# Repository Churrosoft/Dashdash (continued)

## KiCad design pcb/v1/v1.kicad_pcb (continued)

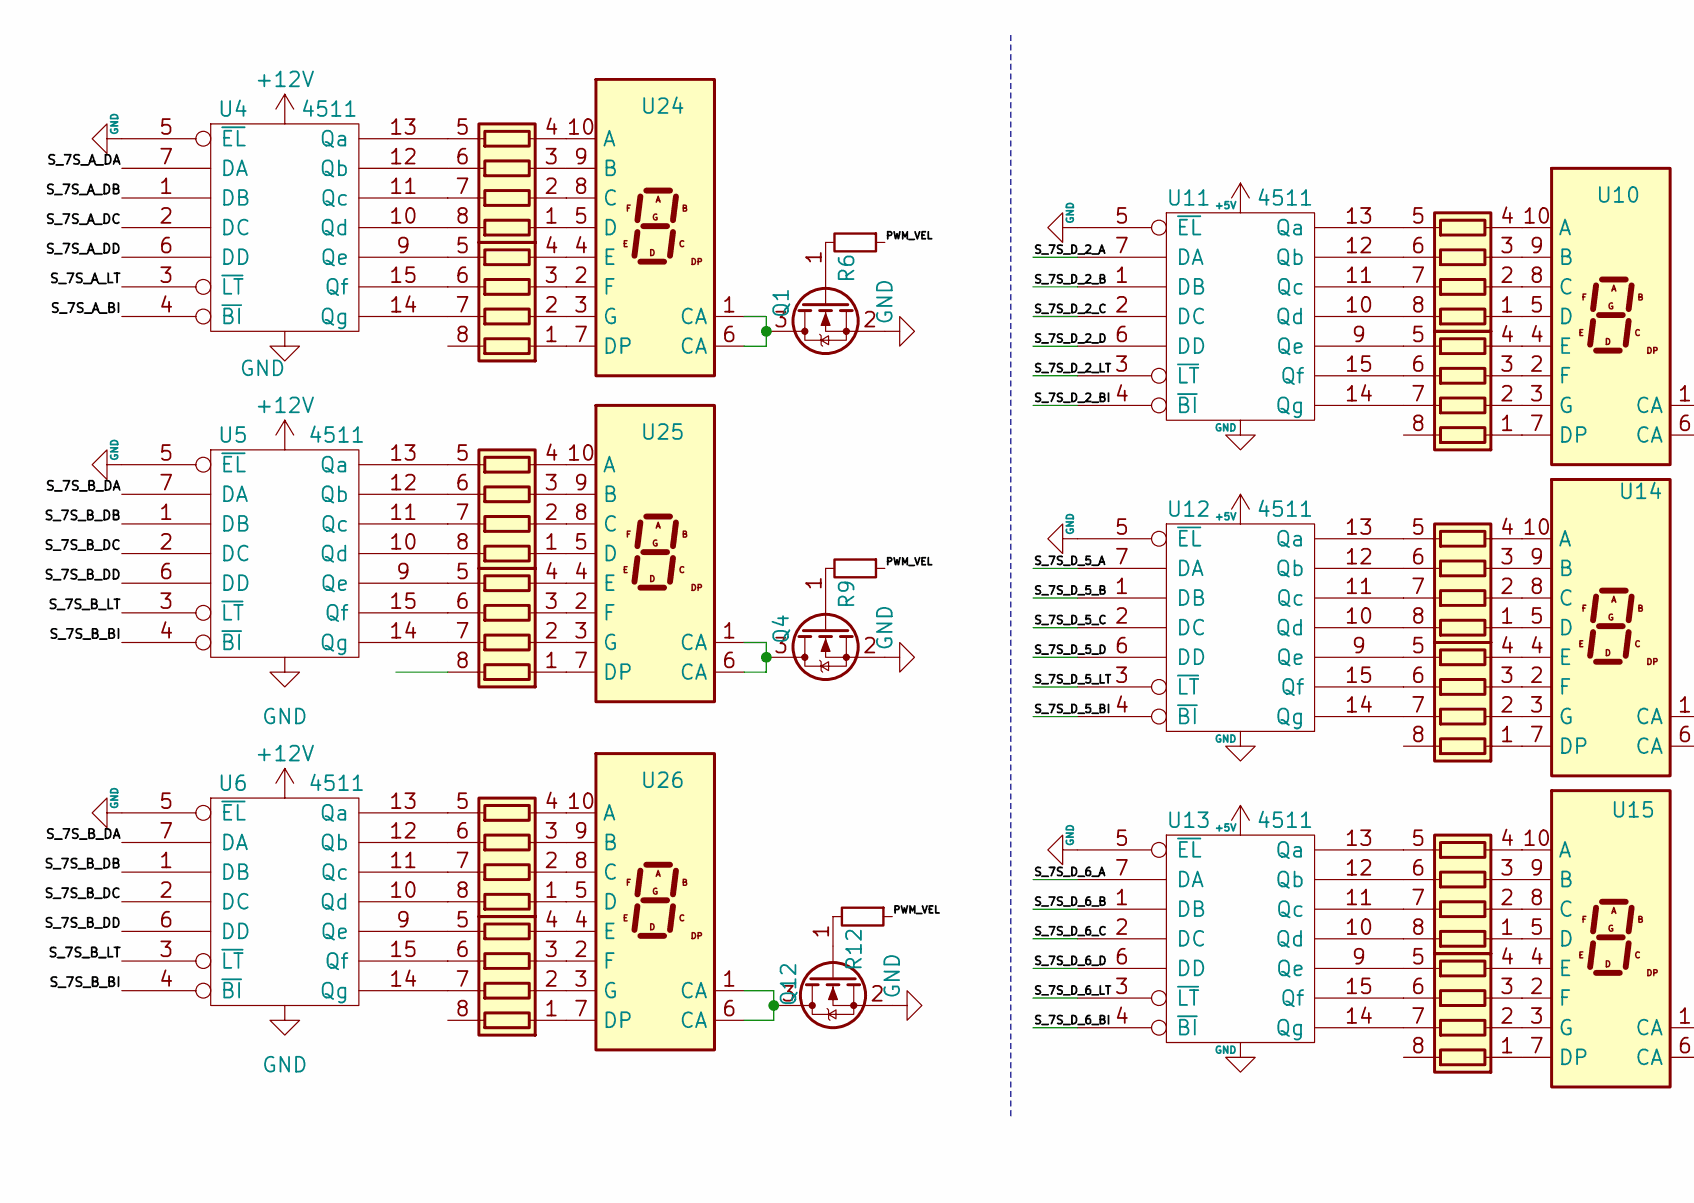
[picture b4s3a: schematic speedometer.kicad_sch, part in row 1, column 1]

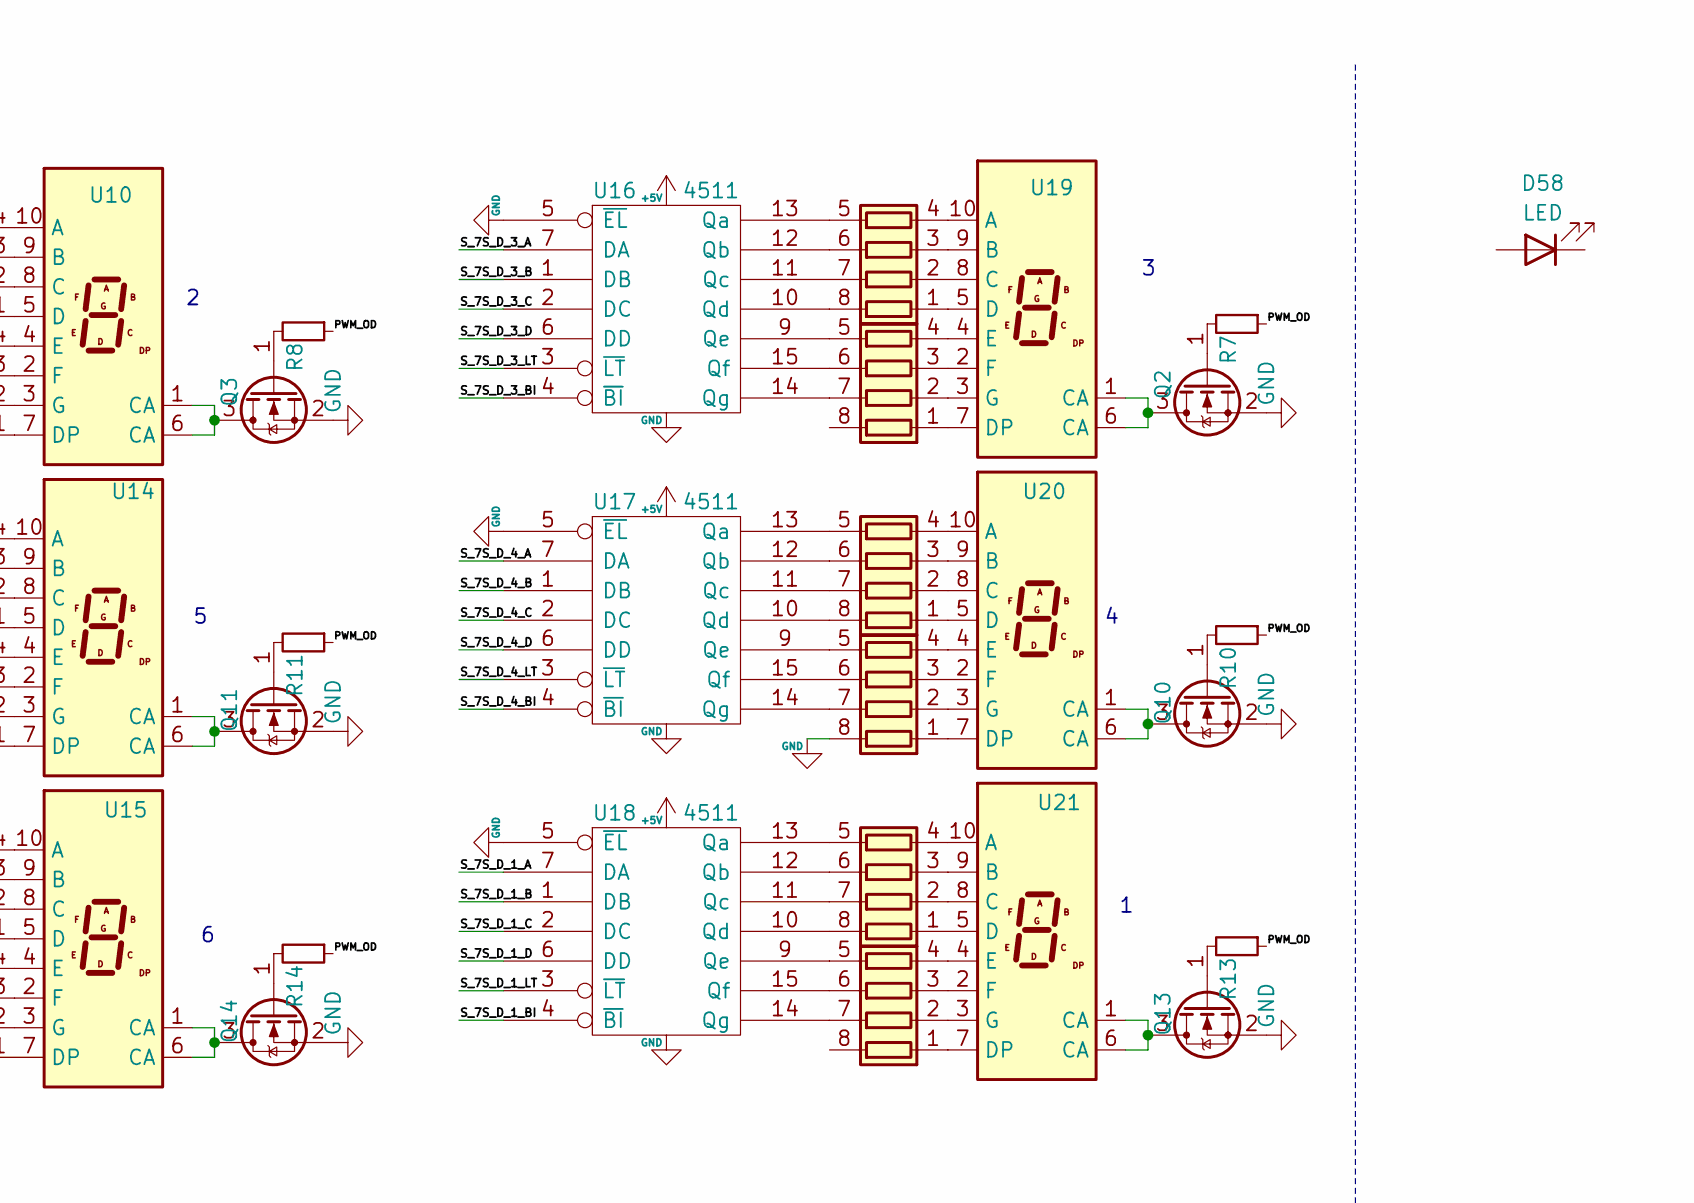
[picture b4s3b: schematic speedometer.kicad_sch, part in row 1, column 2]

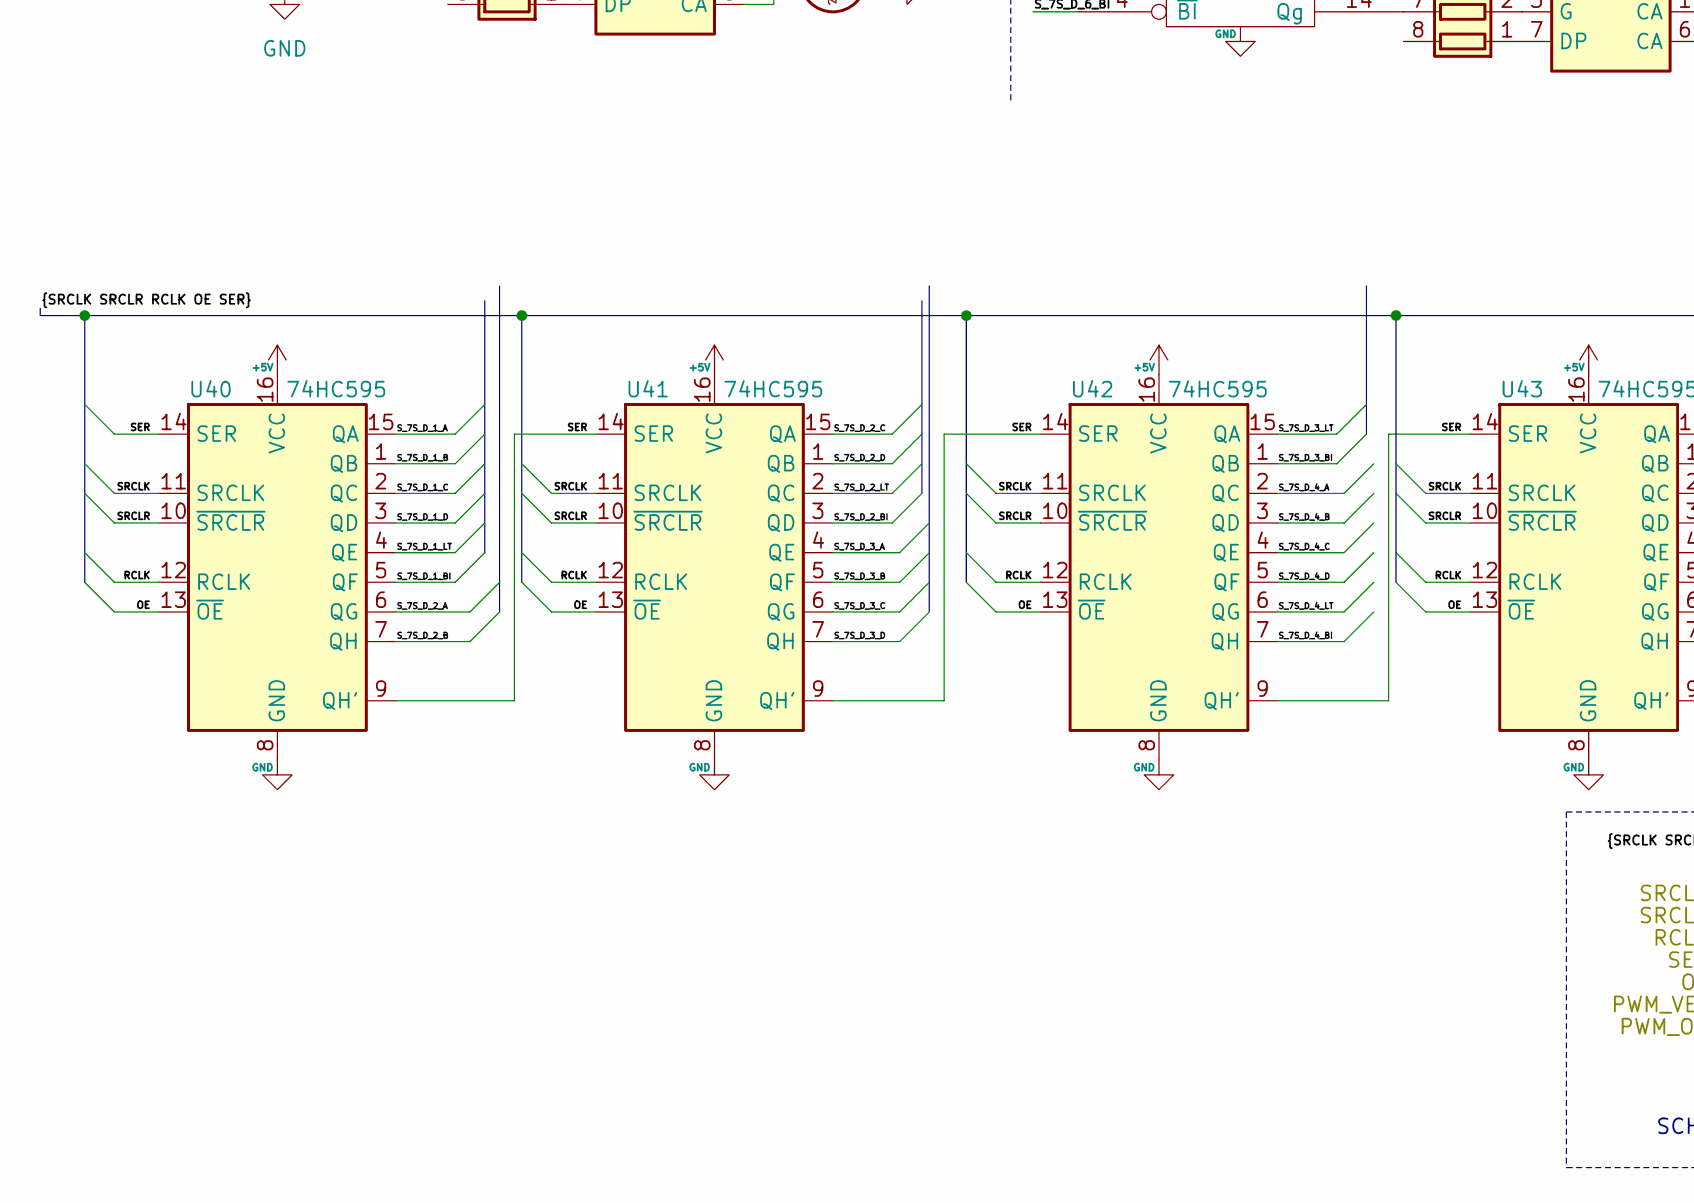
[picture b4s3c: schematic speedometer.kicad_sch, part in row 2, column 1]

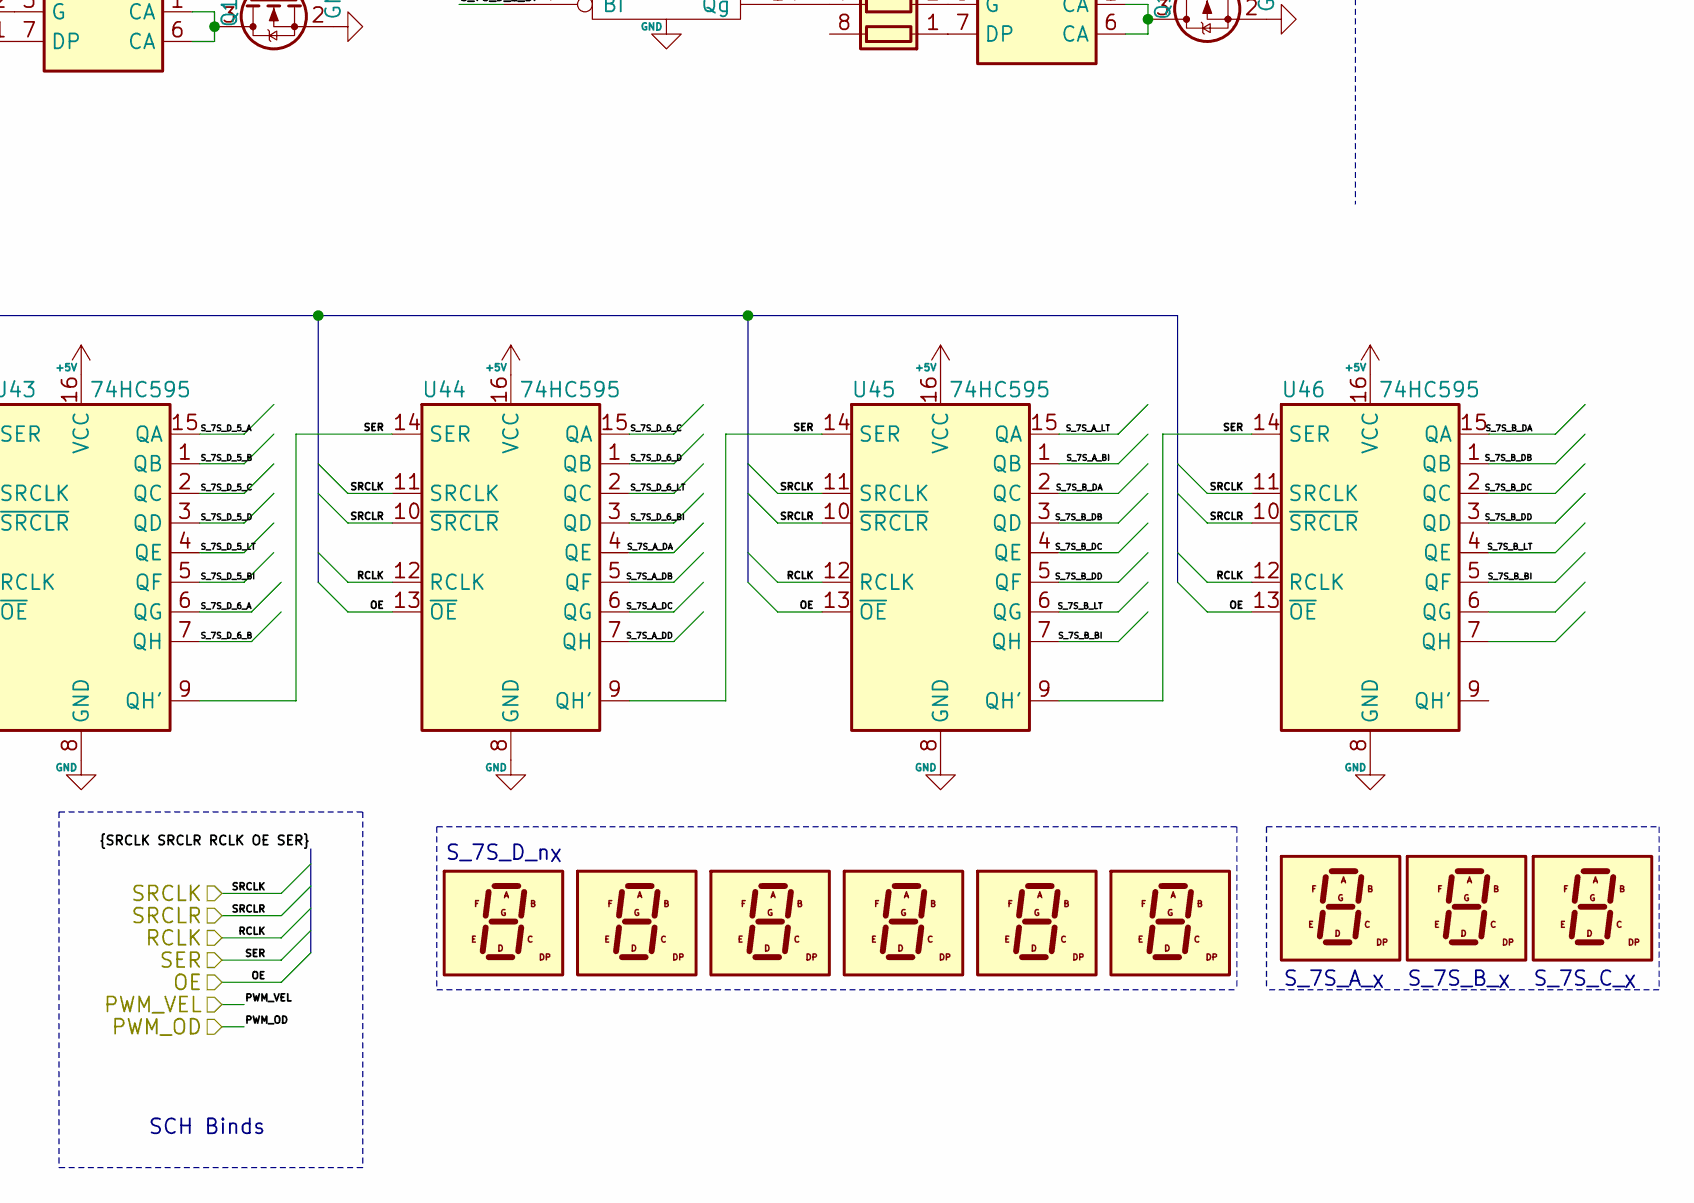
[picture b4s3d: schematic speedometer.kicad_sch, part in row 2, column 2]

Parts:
D58: LED
Q1, Q2, Q3, Q4, Q10, Q11, Q12, Q13, Q14: BSS138; SOT-23
R6, R7, R8, R9, R10, R11, R12, R13, R14: 1k 1/10W +-1%; R_0603_1608Metric; LCSC C217840
RN1, RN2, RN3, RN4, RN5, RN6, RN7, RN8, RN9, RN10, RN11, RN12, RN26, RN27, RN28, RN29, RN30, RN31: 560Ω ±5% 63mW; R_Array_Convex_4x0603; LCSC C253481
U1, U2, U3, U7, U8, U9, U29, U30, U31: KCSC02-123
U4, U5, U6, U11, U12, U13, U16, U17, U18: 4511; TSSOP-16_4.4x5mm_P0.65mm; LCSC C356693
U10, U14, U15, U19, U20, U21: HDSP-7801
U24, U25, U26: HDSP-7801; SA15-11xxx
U40, U41, U42, U43, U44, U45, U46: 74HC595; TSSOP-16_4.4x5mm_P0.65mm; LCSC C5948

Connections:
/PWM_OD: R7.1, R8.1, R10.1, R11.1, R13.1, R14.1; also elsewhere on the board
/PWM_VEL: R6.1, R9.1, R12.1; also elsewhere on the board
/SPEED_OE_L: U40.12 (RCLK), U41.12 (RCLK), U42.12 (RCLK), U43.12 (RCLK), U44.12 (RCLK), U45.12 (RCLK), U46.12 (RCLK)
/SPEED_RCLK_L: U40.10 (~SRCLR), U41.10 (~SRCLR), U42.10 (~SRCLR), U43.10 (~SRCLR), U44.10 (~SRCLR), U45.10 (~SRCLR), U46.10 (~SRCLR)
/SPEED_SER_L: U40.9 (QH'), U40.14 (SER), U41.9 (QH'), U41.14 (SER), U42.9 (QH'), U42.14 (SER), U43.9 (QH'), U43.14 (SER), U44.9 (QH'), U44.14 (SER), U45.9 (QH'), U45.14 (SER), U46.14 (SER)
/SPEED_SRCLK_L: U40.13 (~OE), U41.13 (~OE), U42.13 (~OE), U43.13 (~OE), U44.13 (~OE), U45.13 (~OE), U46.13 (~OE)
/SPEED_SRCLR_L: U40.11 (SRCLK), U41.11 (SRCLK), U42.11 (SRCLK), U43.11 (SRCLK), U44.11 (SRCLK), U45.11 (SRCLK), U46.11 (SRCLK)
/Speedometer/S_7S_A_BI: U4.4 (~BI), U45.1 (QB)
/Speedometer/S_7S_A_DA: U4.7 (DA), U44.4 (QE)
/Speedometer/S_7S_A_DB: U4.1 (DB), U44.5 (QF)
/Speedometer/S_7S_A_DC: U4.2 (DC), U44.6 (QG)
/Speedometer/S_7S_A_DD: U4.6 (DD), U44.7 (QH)
/Speedometer/S_7S_A_LT: U4.3 (~LT), U45.15 (QA)
/Speedometer/S_7S_B_BI: U5.4 (~BI), U6.4 (~BI), U45.7 (QH), U46.5 (QF)
/Speedometer/S_7S_B_DA: U5.7 (DA), U6.7 (DA), U45.2 (QC), U46.15 (QA)
/Speedometer/S_7S_B_DB: U5.1 (DB), U6.1 (DB), U45.3 (QD), U46.1 (QB)
/Speedometer/S_7S_B_DC: U5.2 (DC), U6.2 (DC), U45.4 (QE), U46.2 (QC)
/Speedometer/S_7S_B_DD: U5.6 (DD), U6.6 (DD), U45.5 (QF), U46.3 (QD)
/Speedometer/S_7S_B_LT: U5.3 (~LT), U6.3 (~LT), U45.6 (QG), U46.4 (QE)
/Speedometer/S_7S_D_1_A: U18.7 (DA), U40.15 (QA)
/Speedometer/S_7S_D_1_B: U18.1 (DB), U40.1 (QB)
/Speedometer/S_7S_D_1_BI: U18.4 (~BI), U40.5 (QF)
/Speedometer/S_7S_D_1_C: U18.2 (DC), U40.2 (QC)
/Speedometer/S_7S_D_1_D: U18.6 (DD), U40.3 (QD)
/Speedometer/S_7S_D_1_LT: U18.3 (~LT), U40.4 (QE)
/Speedometer/S_7S_D_2_A: U11.7 (DA), U40.6 (QG)
/Speedometer/S_7S_D_2_B: U11.1 (DB), U40.7 (QH)
/Speedometer/S_7S_D_2_BI: U11.4 (~BI), U41.3 (QD)
/Speedometer/S_7S_D_2_C: U11.2 (DC), U41.15 (QA)
/Speedometer/S_7S_D_2_D: U11.6 (DD), U41.1 (QB)
/Speedometer/S_7S_D_2_LT: U11.3 (~LT), U41.2 (QC)
/Speedometer/S_7S_D_3_A: U16.7 (DA), U41.4 (QE)
/Speedometer/S_7S_D_3_B: U16.1 (DB), U41.5 (QF)
/Speedometer/S_7S_D_3_BI: U16.4 (~BI), U42.1 (QB)
/Speedometer/S_7S_D_3_C: U16.2 (DC), U41.6 (QG)
/Speedometer/S_7S_D_3_D: U16.6 (DD), U41.7 (QH)
/Speedometer/S_7S_D_3_LT: U16.3 (~LT), U42.15 (QA)
/Speedometer/S_7S_D_4_A: U17.7 (DA), U42.2 (QC)
/Speedometer/S_7S_D_4_B: U17.1 (DB), U42.3 (QD)
/Speedometer/S_7S_D_4_BI: U17.4 (~BI), U42.7 (QH)
/Speedometer/S_7S_D_4_C: U17.2 (DC), U42.4 (QE)
/Speedometer/S_7S_D_4_D: U17.6 (DD), U42.5 (QF)
/Speedometer/S_7S_D_4_LT: U17.3 (~LT), U42.6 (QG)
/Speedometer/S_7S_D_5_A: U12.7 (DA), U43.15 (QA)
/Speedometer/S_7S_D_5_B: U12.1 (DB), U43.1 (QB)
/Speedometer/S_7S_D_5_BI: U12.4 (~BI), U43.5 (QF)
/Speedometer/S_7S_D_5_C: U12.2 (DC), U43.2 (QC)
/Speedometer/S_7S_D_5_D: U12.6 (DD), U43.3 (QD)
/Speedometer/S_7S_D_5_LT: U12.3 (~LT), U43.4 (QE)
/Speedometer/S_7S_D_6_A: U13.7 (DA), U43.6 (QG)
/Speedometer/S_7S_D_6_B: U13.1 (DB), U43.7 (QH)
/Speedometer/S_7S_D_6_BI: U13.4 (~BI), U44.3 (QD)
/Speedometer/S_7S_D_6_C: U13.2 (DC), U44.15 (QA)
/Speedometer/S_7S_D_6_D: U13.6 (DD), U44.1 (QB)
/Speedometer/S_7S_D_6_LT: U13.3 (~LT), U44.2 (QC)
GND: Q1.2 (S), Q2.2 (S), Q3.2 (S), Q4.2 (S), Q10.2 (S), Q11.2 (S), Q12.2 (S), Q13.2 (S), Q14.2 (S), RN10.8 (R1.2), U4.5 (~EL), U4.8 (Vss), U5.5 (~EL), U5.8 (Vss), U6.5 (~EL), U6.8 (Vss), U11.5 (~EL), U11.8 (Vss), U12.5 (~EL), U12.8 (Vss), U13.5 (~EL), U13.8 (Vss), U16.5 (~EL), U16.8 (Vss), U17.5 (~EL), U17.8 (Vss), U18.5 (~EL), U18.8 (Vss), U40.8 (GND), U41.8 (GND), U42.8 (GND), U43.8 (GND), U44.8 (GND), U45.8 (GND), U46.8 (GND); also elsewhere on the board
unnamed: Q1.1 (G), R6.2
unnamed: Q1.3 (D), U24.1 (CA), U24.6 (CA)
unnamed: Q2.1 (G), R7.2
unnamed: Q2.3 (D), U19.1 (CA), U19.6 (CA)
unnamed: Q3.1 (G), R8.2
unnamed: Q3.3 (D), U10.1 (CA), U10.6 (CA)
unnamed: Q4.1 (G), R9.2
unnamed: Q4.3 (D), U25.1 (CA), U25.6 (CA)
unnamed: Q10.1 (G), R10.2
unnamed: Q10.3 (D), U20.1 (CA), U20.6 (CA)
unnamed: Q11.1 (G), R11.2
unnamed: Q11.3 (D), U14.1 (CA), U14.6 (CA)
unnamed: Q12.1 (G), R12.2
unnamed: Q12.3 (D), U26.1 (CA), U26.6 (CA)
unnamed: Q13.1 (G), R13.2
unnamed: Q13.3 (D), U21.1 (CA), U21.6 (CA)
unnamed: Q14.1 (G), R14.2
unnamed: Q14.3 (D), U15.1 (CA), U15.6 (CA)
unnamed: RN1.1 (R1.1), U10.5 (D)
unnamed: RN1.2 (R2.1), U10.8 (C)
unnamed: RN1.3 (R3.1), U10.9 (B)
unnamed: RN1.4 (R4.1), U10.10 (A)
unnamed: RN1.5 (R4.2), U11.13 (Qa)
unnamed: RN1.6 (R3.2), U11.12 (Qb)
unnamed: RN1.7 (R2.2), U11.11 (Qc)
unnamed: RN1.8 (R1.2), U11.10 (Qd)
unnamed: RN2.1 (R1.1), U10.7 (DP)
unnamed: RN2.2 (R2.1), U10.3 (G)
unnamed: RN2.3 (R3.1), U10.2 (F)
unnamed: RN2.4 (R4.1), U10.4 (E)
unnamed: RN2.5 (R4.2), U11.9 (Qe)
unnamed: RN2.6 (R3.2), U11.15 (Qf)
unnamed: RN2.7 (R2.2), U11.14 (Qg)
unnamed: RN3.1 (R1.1), U14.5 (D)
unnamed: RN3.2 (R2.1), U14.8 (C)
unnamed: RN3.3 (R3.1), U14.9 (B)
unnamed: RN3.4 (R4.1), U14.10 (A)
unnamed: RN3.5 (R4.2), U12.13 (Qa)
unnamed: RN3.6 (R3.2), U12.12 (Qb)
unnamed: RN3.7 (R2.2), U12.11 (Qc)
unnamed: RN3.8 (R1.2), U12.10 (Qd)
unnamed: RN4.1 (R1.1), U14.7 (DP)
unnamed: RN4.2 (R2.1), U14.3 (G)
unnamed: RN4.3 (R3.1), U14.2 (F)
unnamed: RN4.4 (R4.1), U14.4 (E)
unnamed: RN4.5 (R4.2), U12.9 (Qe)
unnamed: RN4.6 (R3.2), U12.15 (Qf)
unnamed: RN4.7 (R2.2), U12.14 (Qg)
unnamed: RN5.1 (R1.1), U15.5 (D)
unnamed: RN5.2 (R2.1), U15.8 (C)
unnamed: RN5.3 (R3.1), U15.9 (B)
unnamed: RN5.4 (R4.1), U15.10 (A)
unnamed: RN5.5 (R4.2), U13.13 (Qa)
unnamed: RN5.6 (R3.2), U13.12 (Qb)
unnamed: RN5.7 (R2.2), U13.11 (Qc)
unnamed: RN5.8 (R1.2), U13.10 (Qd)
unnamed: RN6.1 (R1.1), U15.7 (DP)
unnamed: RN6.2 (R2.1), U15.3 (G)
unnamed: RN6.3 (R3.1), U15.2 (F)
unnamed: RN6.4 (R4.1), U15.4 (E)
unnamed: RN6.5 (R4.2), U13.9 (Qe)
unnamed: RN6.6 (R3.2), U13.15 (Qf)
unnamed: RN6.7 (R2.2), U13.14 (Qg)
unnamed: RN7.1 (R1.1), U19.5 (D)
unnamed: RN7.2 (R2.1), U19.8 (C)
unnamed: RN7.3 (R3.1), U19.9 (B)
unnamed: RN7.4 (R4.1), U19.10 (A)
unnamed: RN7.5 (R4.2), U16.13 (Qa)
unnamed: RN7.6 (R3.2), U16.12 (Qb)
unnamed: RN7.7 (R2.2), U16.11 (Qc)
unnamed: RN7.8 (R1.2), U16.10 (Qd)
unnamed: RN8.1 (R1.1), U19.7 (DP)
unnamed: RN8.2 (R2.1), U19.3 (G)
unnamed: RN8.3 (R3.1), U19.2 (F)
unnamed: RN8.4 (R4.1), U19.4 (E)
unnamed: RN8.5 (R4.2), U16.9 (Qe)
unnamed: RN8.6 (R3.2), U16.15 (Qf)
unnamed: RN8.7 (R2.2), U16.14 (Qg)
unnamed: RN9.1 (R1.1), U20.5 (D)
unnamed: RN9.2 (R2.1), U20.8 (C)
unnamed: RN9.3 (R3.1), U20.9 (B)
unnamed: RN9.4 (R4.1), U20.10 (A)
unnamed: RN9.5 (R4.2), U17.13 (Qa)
unnamed: RN9.6 (R3.2), U17.12 (Qb)
unnamed: RN9.7 (R2.2), U17.11 (Qc)
unnamed: RN9.8 (R1.2), U17.10 (Qd)
unnamed: RN10.1 (R1.1), U20.7 (DP)
unnamed: RN10.2 (R2.1), U20.3 (G)
unnamed: RN10.3 (R3.1), U20.2 (F)
unnamed: RN10.4 (R4.1), U20.4 (E)
unnamed: RN10.5 (R4.2), U17.9 (Qe)
unnamed: RN10.6 (R3.2), U17.15 (Qf)
unnamed: RN10.7 (R2.2), U17.14 (Qg)
unnamed: RN11.1 (R1.1), U21.5 (D)
unnamed: RN11.2 (R2.1), U21.8 (C)
unnamed: RN11.3 (R3.1), U21.9 (B)
unnamed: RN11.4 (R4.1), U21.10 (A)
unnamed: RN11.5 (R4.2), U18.13 (Qa)
unnamed: RN11.6 (R3.2), U18.12 (Qb)
unnamed: RN11.7 (R2.2), U18.11 (Qc)
unnamed: RN11.8 (R1.2), U18.10 (Qd)
unnamed: RN12.1 (R1.1), U21.7 (DP)
unnamed: RN12.2 (R2.1), U21.3 (G)
unnamed: RN12.3 (R3.1), U21.2 (F)
unnamed: RN12.4 (R4.1), U21.4 (E)
unnamed: RN12.5 (R4.2), U18.9 (Qe)
unnamed: RN12.6 (R3.2), U18.15 (Qf)
unnamed: RN12.7 (R2.2), U18.14 (Qg)
unnamed: RN26.1 (R1.1), U24.5 (D)
unnamed: RN26.2 (R2.1), U24.8 (C)
unnamed: RN26.3 (R3.1), U24.9 (B)
unnamed: RN26.4 (R4.1), U24.10 (A)
unnamed: RN26.5 (R4.2), U4.13 (Qa)
unnamed: RN26.6 (R3.2), U4.12 (Qb)
unnamed: RN26.7 (R2.2), U4.11 (Qc)
unnamed: RN26.8 (R1.2), U4.10 (Qd)
unnamed: RN27.1 (R1.1), U24.7 (DP)
unnamed: RN27.2 (R2.1), U24.3 (G)
unnamed: RN27.3 (R3.1), U24.2 (F)
unnamed: RN27.4 (R4.1), U24.4 (E)
unnamed: RN27.5 (R4.2), U4.9 (Qe)
unnamed: RN27.6 (R3.2), U4.15 (Qf)
unnamed: RN27.7 (R2.2), U4.14 (Qg)
unnamed: RN28.1 (R1.1), U25.5 (D)
unnamed: RN28.2 (R2.1), U25.8 (C)
unnamed: RN28.3 (R3.1), U25.9 (B)
unnamed: RN28.4 (R4.1), U25.10 (A)
unnamed: RN28.5 (R4.2), U5.13 (Qa)
unnamed: RN28.6 (R3.2), U5.12 (Qb)
unnamed: RN28.7 (R2.2), U5.11 (Qc)
unnamed: RN28.8 (R1.2), U5.10 (Qd)
unnamed: RN29.1 (R1.1), U25.7 (DP)
unnamed: RN29.2 (R2.1), U25.3 (G)
unnamed: RN29.3 (R3.1), U25.2 (F)
unnamed: RN29.4 (R4.1), U25.4 (E)
unnamed: RN29.5 (R4.2), U5.9 (Qe)
unnamed: RN29.6 (R3.2), U5.15 (Qf)
unnamed: RN29.7 (R2.2), U5.14 (Qg)
unnamed: RN30.1 (R1.1), U26.5 (D)
unnamed: RN30.2 (R2.1), U26.8 (C)
unnamed: RN30.3 (R3.1), U26.9 (B)
unnamed: RN30.4 (R4.1), U26.10 (A)
unnamed: RN30.5 (R4.2), U6.13 (Qa)
unnamed: RN30.6 (R3.2), U6.12 (Qb)
unnamed: RN30.7 (R2.2), U6.11 (Qc)
unnamed: RN30.8 (R1.2), U6.10 (Qd)
unnamed: RN31.1 (R1.1), U26.7 (DP)
unnamed: RN31.2 (R2.1), U26.3 (G)
unnamed: RN31.3 (R3.1), U26.2 (F)
unnamed: RN31.4 (R4.1), U26.4 (E)
unnamed: RN31.5 (R4.2), U6.9 (Qe)
unnamed: RN31.6 (R3.2), U6.15 (Qf)
unnamed: RN31.7 (R2.2), U6.14 (Qg)

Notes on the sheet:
SCH Binds
S_7S_D_n_{X}
S_7S_A__{X}
S_7S_B__{X}
S_7S_C__{X}

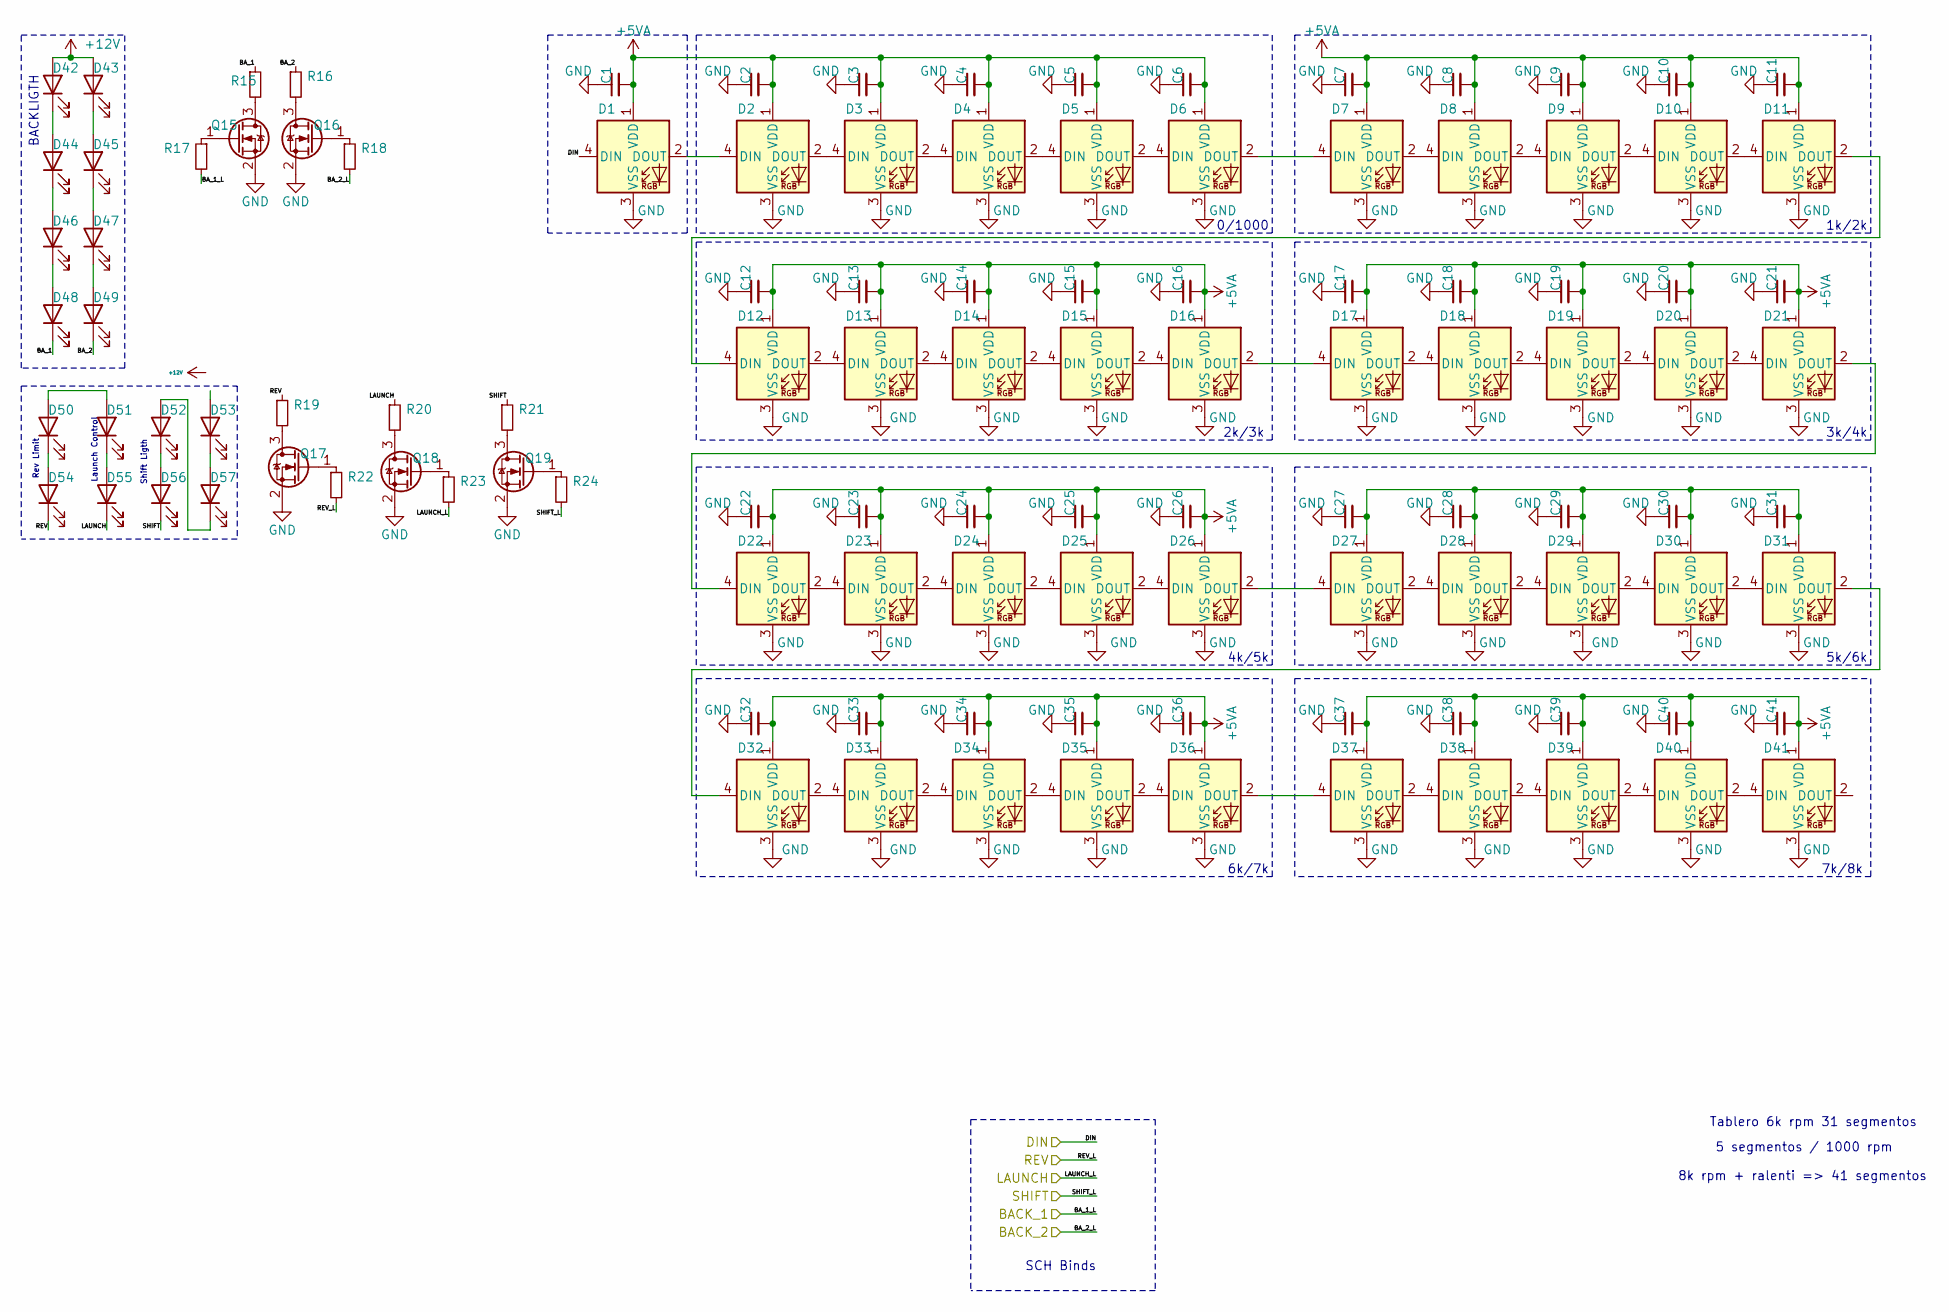
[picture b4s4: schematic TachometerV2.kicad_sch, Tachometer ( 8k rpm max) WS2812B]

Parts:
C1, C2, C3, C4, C5, C6, C7, C8, C9, C10, C11, C12, C13, C14, C15, C16, C17, C18, C19, C20, C21, C22, C23, C24, C25, C26, C27, C28, C29, C30, C31, C32, C33, C34, C35, C36, C37, C38, C39, C40, C41: 100nF; C_0805_2012Metric; LCSC C49678
D1, D2, D3, D4, D5, D6, D7, D8, D9, D10, D11, D12, D13, D14, D15, D16, D17, D18, D19, D20, D21, D22, D23, D24, D25, D26, D27, D28, D29, D30, D31, D32, D33, D34, D35, D36, D37, D38, D39, D40, D41: WS2812B; LED_SK6812MINI_PLCC4_3.5x3.5mm_P1.75mm
D42, D43, D44, D45, D46, D47, D48, D49, D50, D51, D52, D53, D54, D55, D56, D57: LED; LED_0805_2012Metric_Castellated; LCSC C205447
Q15, Q16, Q17, Q18, Q19: BSS138; SOT-23
R15, R16, R17, R18, R19, R20, R21, R22, R23, R24: 1k 1/10W +-1%; R_0603_1608Metric; LCSC C217840

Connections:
+5VA: C1.2, C2.2, C3.2, C4.2, C5.2, C6.2, C7.2, C8.2, C9.2, C10.2, C11.2, C12.2, C13.2, C14.2, C15.2, C16.2, C17.2, C18.2, C19.2, C20.2, C21.2, C22.2, C23.2, C24.2, C25.2, C26.2, C32.2, C33.2, C34.2, C35.2, C36.2, C37.2, C38.2, C39.2, C40.2, C41.2, D1.1 (VDD), D2.1 (VDD), D3.1 (VDD), D4.1 (VDD), D5.1 (VDD), D6.1 (VDD), D7.1 (VDD), D8.1 (VDD), D9.1 (VDD), D10.1 (VDD), D11.1 (VDD), D12.1 (VDD), D13.1 (VDD), D14.1 (VDD), D15.1 (VDD), D16.1 (VDD), D17.1 (VDD), D18.1 (VDD), D19.1 (VDD), D20.1 (VDD), D21.1 (VDD), D22.1 (VDD), D23.1 (VDD), D24.1 (VDD), D25.1 (VDD), D26.1 (VDD), D32.1 (VDD), D33.1 (VDD), D34.1 (VDD), D35.1 (VDD), D36.1 (VDD), D37.1 (VDD), D38.1 (VDD), D39.1 (VDD), D40.1 (VDD), D41.1 (VDD)
/PWM_BACK_1: R17.2; also elsewhere on the board
/PWM_BACK_2: R18.2; also elsewhere on the board
/TCH_DIN: D1.4 (DIN); also elsewhere on the board
/TCH_LAUNCH: D55.1 (K), R20.1, R23.2; also elsewhere on the board
/TCH_REV: D54.1 (K), R19.1, R22.2; also elsewhere on the board
/TCH_SHIFT: D56.1 (K), R21.1, R24.2; also elsewhere on the board
/TachometerV2/BA_1: D48.1 (K), R15.1
/TachometerV2/BA_2: D49.1 (K), R16.1
GND: C1.1, C2.1, C3.1, C4.1, C5.1, C6.1, C7.1, C8.1, C9.1, C10.1, C11.1, C12.1, C13.1, C14.1, C15.1, C16.1, C17.1, C18.1, C19.1, C20.1, C21.1, C22.1, C23.1, C24.1, C25.1, C26.1, C27.1, C28.1, C29.1, C30.1, C31.1, C32.1, C33.1, C34.1, C35.1, C36.1, C37.1, C38.1, C39.1, C40.1, C41.1, D1.3 (VSS), D2.3 (VSS), D3.3 (VSS), D4.3 (VSS), D5.3 (VSS), D6.3 (VSS), D7.3 (VSS), D8.3 (VSS), D9.3 (VSS), D10.3 (VSS), D11.3 (VSS), D12.3 (VSS), D13.3 (VSS), D14.3 (VSS), D15.3 (VSS), D16.3 (VSS), D17.3 (VSS), D18.3 (VSS), D19.3 (VSS), D20.3 (VSS), D21.3 (VSS), D22.3 (VSS), D23.3 (VSS), D24.3 (VSS), D25.3 (VSS), D26.3 (VSS), D27.3 (VSS), D28.3 (VSS), D29.3 (VSS), D30.3 (VSS), D31.3 (VSS), D32.3 (VSS), D33.3 (VSS), D34.3 (VSS), D35.3 (VSS), D36.3 (VSS), D37.3 (VSS), D38.3 (VSS), D39.3 (VSS), D40.3 (VSS), D41.3 (VSS), Q15.2 (S), Q16.2 (S), Q17.2 (S), Q18.2 (S), Q19.2 (S); also elsewhere on the board
unnamed: C27.2, C28.2, C29.2, C30.2, C31.2, D27.1 (VDD), D28.1 (VDD), D29.1 (VDD), D30.1 (VDD), D31.1 (VDD)
unnamed: D1.2 (DOUT), D2.4 (DIN)
unnamed: D2.2 (DOUT), D3.4 (DIN)
unnamed: D3.2 (DOUT), D4.4 (DIN)
unnamed: D4.2 (DOUT), D5.4 (DIN)
unnamed: D5.2 (DOUT), D6.4 (DIN)
unnamed: D6.2 (DOUT), D7.4 (DIN)
unnamed: D7.2 (DOUT), D8.4 (DIN)
unnamed: D8.2 (DOUT), D9.4 (DIN)
unnamed: D10.2 (DOUT), D11.4 (DIN)
unnamed: D9.2 (DOUT), D10.4 (DIN)
unnamed: D11.2 (DOUT), D12.4 (DIN)
unnamed: D12.2 (DOUT), D13.4 (DIN)
unnamed: D13.2 (DOUT), D14.4 (DIN)
unnamed: D14.2 (DOUT), D15.4 (DIN)
unnamed: D15.2 (DOUT), D16.4 (DIN)
unnamed: D16.2 (DOUT), D17.4 (DIN)
unnamed: D17.2 (DOUT), D18.4 (DIN)
unnamed: D18.2 (DOUT), D19.4 (DIN)
unnamed: D19.2 (DOUT), D20.4 (DIN)
unnamed: D20.2 (DOUT), D21.4 (DIN)
unnamed: D21.2 (DOUT), D22.4 (DIN)
unnamed: D22.2 (DOUT), D23.4 (DIN)
unnamed: D23.2 (DOUT), D24.4 (DIN)
unnamed: D24.2 (DOUT), D25.4 (DIN)
unnamed: D25.2 (DOUT), D26.4 (DIN)
unnamed: D26.2 (DOUT), D27.4 (DIN)
unnamed: D27.2 (DOUT), D28.4 (DIN)
unnamed: D28.2 (DOUT), D29.4 (DIN)
unnamed: D29.2 (DOUT), D30.4 (DIN)
unnamed: D30.2 (DOUT), D31.4 (DIN)
unnamed: D31.2 (DOUT), D32.4 (DIN)
unnamed: D32.2 (DOUT), D33.4 (DIN)
unnamed: D33.2 (DOUT), D34.4 (DIN)
unnamed: D34.2 (DOUT), D35.4 (DIN)
unnamed: D35.2 (DOUT), D36.4 (DIN)
unnamed: D36.2 (DOUT), D37.4 (DIN)
unnamed: D37.2 (DOUT), D38.4 (DIN)
unnamed: D38.2 (DOUT), D39.4 (DIN)
unnamed: D39.2 (DOUT), D40.4 (DIN)
unnamed: D40.2 (DOUT), D41.4 (DIN)
unnamed: D42.1 (K), D44.2 (A)
unnamed: D43.1 (K), D45.2 (A)
unnamed: D44.1 (K), D46.2 (A)
unnamed: D45.1 (K), D47.2 (A)
unnamed: D46.1 (K), D48.2 (A)
unnamed: D47.1 (K), D49.2 (A)
unnamed: D50.1 (K), D54.2 (A)
unnamed: D50.2 (A), D51.2 (A)
unnamed: D51.1 (K), D55.2 (A)
unnamed: D52.1 (K), D56.2 (A)
unnamed: D52.2 (A), D57.1 (K)
unnamed: D53.1 (K), D57.2 (A)
unnamed: Q15.1 (G), R17.1
unnamed: Q15.3 (D), R15.2
unnamed: Q16.1 (G), R18.1
unnamed: Q16.3 (D), R16.2
unnamed: Q17.1 (G), R22.1
unnamed: Q17.3 (D), R19.2
unnamed: Q18.1 (G), R23.1
unnamed: Q18.3 (D), R20.2
unnamed: Q19.1 (G), R24.1
unnamed: Q19.3 (D), R21.2

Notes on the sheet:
BACKLIGTH
Rev Limit
Launch Control
Shift Ligth
SCH Binds
2k/3k
0/1000
4k/5k
6k/7k
7k/8k
1k/2k
3k/4k
5k/6k
5 segmentos / 1000 rpm
Tablero 6k rpm 31 segmentos
8k rpm + ralenti => 41 segmentos

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
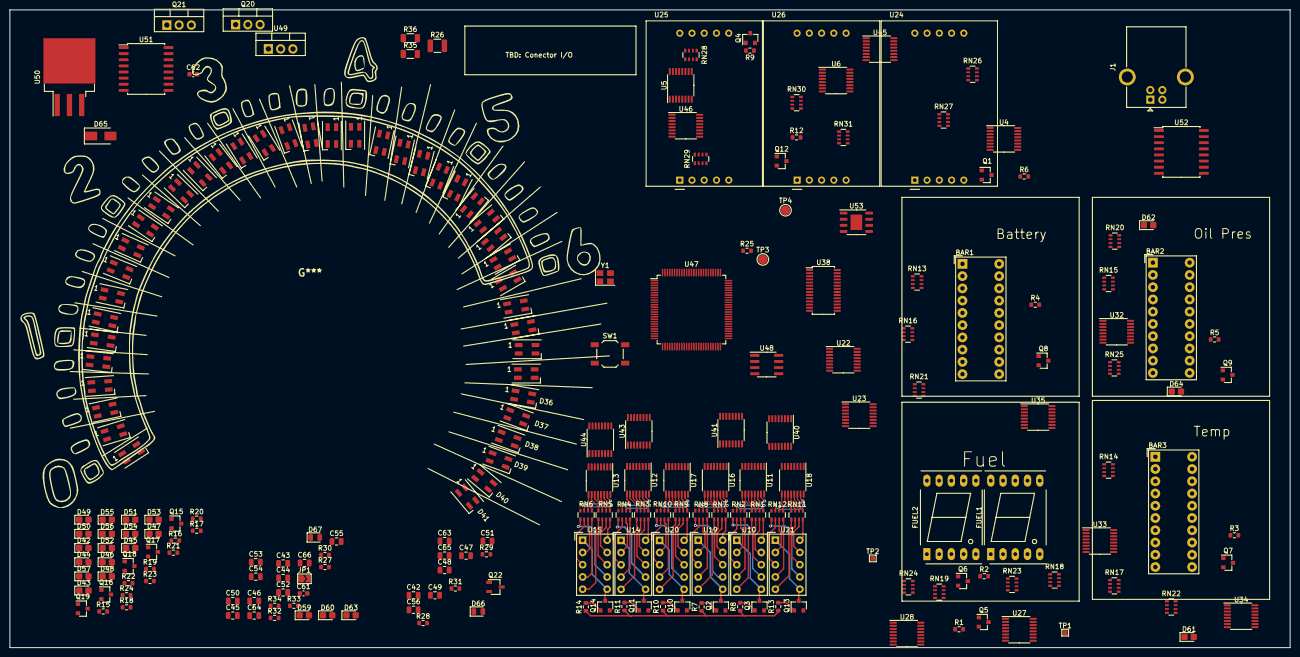
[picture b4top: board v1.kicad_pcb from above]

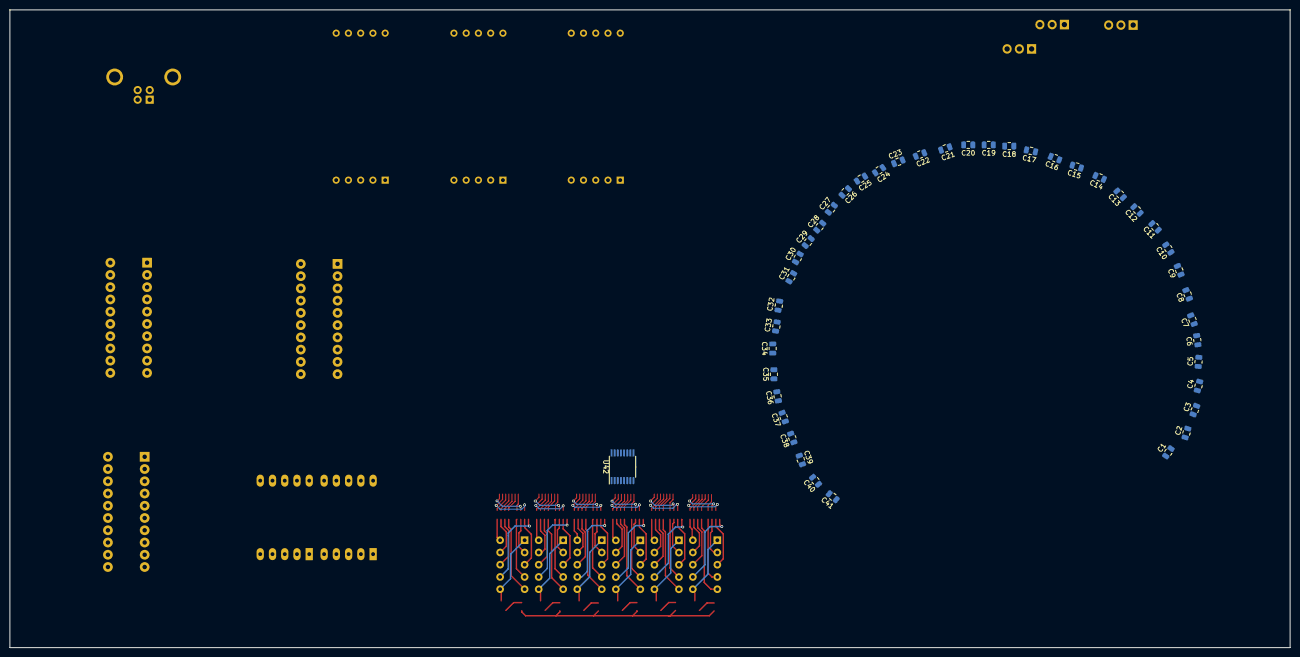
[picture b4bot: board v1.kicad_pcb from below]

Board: 2 copper layers, 265.5 x 132.2 mm, 271 parts (42 on the bottom side), 455 nets.

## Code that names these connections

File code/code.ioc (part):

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PD12.GPIO_Label=SPEED_SER
PC7.GPIOParameters=GPIO_Label
PH0-OSC_IN.Signal=RCC_OSC_IN
PE11.GPIOParameters=GPIO_Label
Mcu.UserName=STM32F405VGTx
PE11.GPIO_Label=BFT_SRCLK
PC6.GPIO_Label=TCH_DIN
PA11.Mode=Device_Only
RCC.SYSCLKSource=RCC_SYSCLKSOURCE_PLLCLK
PD13.Signal=GPIO_Output
PA12.Signal=USB_OTG_FS_DP
PD15.GPIOParameters=GPIO_Label
PD11.GPIO_Label=SPEED_OE
PB6.Signal=I2C1_SCL
PC7.Signal=GPIO_Output
PB6.Mode=I2C
PD0.Signal=CAN1_RX
PH0-OSC_IN.Mode=HSE-External-Oscillator
RCC.HSE_VALUE=25000000
PB3.Mode=Full_Duplex_Master
PB4.Mode=Full_Duplex_Master
PE9.Signal=GPIO_Output
PB5.Mode=Full_Duplex_Master
PB7.Signal=I2C1_SDA
PA8.Signal=RCC_MCO_1
PE10.Signal=GPIO_Output
PH1-OSC_OUT.Mode=HSE-External-Oscillator
PB7.GPIO_Label=I2C1_SDA
PC8.GPIOParameters=GPIO_Label
PD13.GPIO_Label=SPEED_RCLK
Mcu.Package=LQFP100
PB1.Signal=ADCx_IN9
PA6.Signal=ADCx_IN6
PE10.GPIOParameters=GPIO_Label
PD12.Signal=GPIO_Output
PE7.Signal=GPIO_Output
PE10.GPIO_Label=BFT_SRCLR
PD15.Signal=GPIO_Output
PB4.Signal=SPI1_MISO
PA3.Signal=ADCx_IN3
PE8.GPIOParameters=GPIO_Label
PD15.GPIO_Label=SPEED_SRCLK
PC9.GPIO_Label=TCH_REV
PC8.Signal=GPIO_Output
PC6.Signal=GPIO_Output
PD13.GPIOParameters=GPIO_Label
PD1.Signal=CAN1_TX
PA0-WKUP.Signal=ADCx_IN0
PE9.GPIOParameters=GPIO_Label
PC8.GPIO_Label=TCH_LAUNCH
PA9.Mode=Activate_VBUS
PD12.GPIOParameters=GPIO_Label
PE7.GPIOParameters=GPIO_Label
PB7.GPIOParameters=GPIO_Label
PE8.GPIO_Label=BFT_SER
PA9.Signal=USB_OTG_FS_VBUS
PE11.Signal=GPIO_Output
PE9.GPIO_Label=BFT_RCLK
PA1.Signal=ADCx_IN1
PA5.Signal=ADCx_IN5
board=custom
PD1.Mode=CAN_Activate
PD11.GPIOParameters=GPIO_Label
PE8.Signal=GPIO_Output
PH1-OSC_OUT.Signal=RCC_OSC_OUT
PD14.GPIO_Label=SPEED_SRCLR
PC9.GPIOParameters=GPIO_Label
Mcu.Name=STM32F405VGTx
PE7.GPIO_Label=BFT_OE
PD0.Mode=CAN_Activate
PA2.Signal=ADCx_IN2
PD14.Signal=GPIO_Output
PC7.GPIO_Label=TCH_SHIFT
PB3.Signal=SPI1_SCK
PA4.Signal=ADCx_IN4
PD14.GPIOParameters=GPIO_Label
RCC.SYSCLKFreq_VALUE=168000000
PB5.Signal=SPI1_MOSI
PA12.Mode=Device_Only
PD11.Signal=GPIO_Output
PB7.Mode=I2C
PA11.Signal=USB_OTG_FS_DM
PC6.GPIOParameters=GPIO_Label
PA8.Mode=Clock-out-1
PC9.Signal=GPIO_Output
PB0.Signal=ADCx_IN8
PA7.Signal=ADCx_IN7

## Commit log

2021-05-07 Added Tachometer sch, init on Speedometer sch
2021-10-01 end v1, move to modular design
2022-04-18 init v2
2022-07-15 main board sch
2022-07-15 ESD SPI
2022-07-15 add powaaaaaa
2022-07-16 Add external modules connector
2022-07-20 routing can/usb/power/leds/flash
2022-07-21 routing
2022-07-23 tachometer, add neopixels
2022-07-23 routing neopixel
2022-07-27 tach v2, routing & 3D
2022-07-27 routing spi flash
2022-08-02 routing backlight leds
2022-08-03 rpm routing v01
2022-08-03 update neopixel
